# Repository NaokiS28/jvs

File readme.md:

# JVS ArduinIO
This is a WIP library for communicating over the JVS protocol in Arduino compatible boards. This library supports both host mode and device mode. It requires one hardware UART to work connected to an RS485 transceiver such as the MAX RS485 TTL converter module.

A host can only have 1 input port per instance, a device must have 1 ouput port but may optionally have an input port for daisy chaning IO devices. The data lines are connected between ports, the sense line must connect to an output for the output port and an input for the input port. You will also need to connect the sense pin to pin 1 of USB-A connector.

# Hardware
## Device mode
This library requires a MAX485 transceiver or equivalent connected to the serial port RX and TX pins. You also need to specify an RTS (Request to Send) pin which is connected to both DE and ~RE.

Finally, you will either need a transistor (BC547 or 2n2222 or eqv.) for pulling the sense line low; whilst you can use the IO pin directly, it is better practice to do it this way to protect your MCU and the library would need to be changed to uninvert the pin. The sense line needs to be at 2.5v with the ID unset, and it's recomended to use 4x 1n4007 diodes from the sense line to ground to acheive this but users have reported a 1K resistor will also work - This will depend entirely on the host you are using.

Optionally you can specify a sense input line but this isn't unless you are supporting daisy chaining. If you are, you need a way to automatically terminate or remove the termination resistors from the bus. The bus must be terminated if there is no secondary IO board attached. It must *not* be terminated if there is a secondary IO board attached to your device.

Here is an example with downstream IO sensing which is needed for daisychaining.

## Host mode
In host mode, it is advised to use an LM393 opamp to handle 5V, 2.5v and 0v sensing. This allows one to use either two pin or one pin to sense IO status (present with/out ID, not present). Otherwise, you can connect this to a GPIO pin, perhaps use a 220Ω resistor in line for over current protection.

### Sensing
Depending on how you want to sense IO boards, you will need to consider different methods of sensing the IO board attached.

The SEGA/Nintendo/Namco Triforce does single pin sensing which is good enough for most use cases:

Another option is to remove the buffer gate and use two pins for better sensing. This allows one to know exactly the state of the sense in pin, be it IO board not connected, IO is present with no ID or present and ID'd. The SEGA Chihiro uses a verison of this sensing:

# Usage
To use the library, include it before setup and then declare an instance by passing a UART port and the sense pin input/output. On Arduino UNO this will be Serial, but on board with multiple serial ports, you can use Serial2, Serial 3 etc. You cannot use SerialUSB. **Note you can only have one instance at one time**.
```
#include "jvs.h"
JVS jvs(Serial, 2, 3);     // HardwareSerial port, Sense pin, RTS pin
```
Once delcared, you will then need to run the initialization routines at startup either as a host node or a device node.
```
// Init as Device
void setup(){
    jvs.begin(DEVICE_NODE);    // Begin as device node
    jvs.initDevice();
}
```
```
// Init as Host
void setup(){
    jvs.begin(HOST_NODE);    // Begin as host node
    int found = jvs.initHost();       // Will hang here until devices are assigned or there is no JVS nodes. Returns number of JVS nodes
    //Serial1.print("Found: ");
    //Serial1.print(found);
    //Serial1.println(" nodes");
}
```
Then you will need to put update() in your loop. This is so you can receive packets from the IO board. You can have the JVS library run command codes, so long as it's in device mode and have set the iput/output data arrays:
```
void loop(){
    if(jvs.update()){
        jvs.runCommand();
    }
}
```
Or you can read the data in manually:
```
void loop(){
    if(jvs.update()){
        JVS_Frame inFrame;      // Frame in
        inFrame = jvs.read();   // Read frame into buffer
    }
}
```

## Data Storage/JVS Frame layout
The data for commands and arguments is stored in JVS_Frame.data:
```
struct JVS_Frame {
    uint8_t sync = 0xE0;            // Sync is always E0
    uint8_t nodeID = 0;             // Node that frame is intended for, 0xFF is a boradcast frame
    uint8_t numBytes = 0;           // Includes all subsequent bytes (Status, data and sum) in frame after this byte
    uint8_t statusCode = 1;
    union{
        uint8_t data [254] = {0};   // Is command and parameters from host, report and results from device
        uint16_t data16 [127];      // Some parameters are 16-bit ints
        char dataString [102];      // When reading node IDs, they are stored as ASCII
    } ;
    uint8_t sum = 0;                // Checksum of ID, numbytes, data bytes
    uint8_t cmdCount = 1;           // Number of commands counted. Only counts standard commands (not manufacturer specific)
};
```

## JVS Info
Both host and device nodes will need some data to report back when requested. The host needs the game name filled in where as devices need to report their name and what features it supports. If no data is supplied, it is prefilled with generic data. **Note: When set as device, _ident is used where as _mainID is used when set to host**. It's worth noting that only Namco games/devices seem to care about the main board ID, you can choose to support it or not, but Namco games might not be happy if you don't support it.

The library supports storing JVS IO board data in the following struct. This can be used for multiple IO boards by delcaring an array.
```
struct JVS_Info {
    char ident[100] = {"JVS ArduinIO;github.com/NaokiS28/jvs;VER:0.1 Beta"};
    char mainID[100] = {"ArduinoIO Host;github.com/NaokiS28/jvs;VER:0.1 Beta"};
    uint8_t cmdRev = 11;            // Stored as BCD, some JVS hosts (Triforce) will report ver 0.0 if it's higher than 1.1
    uint8_t jvsRev = 30;            // Stored as BCD, JVS rev. 20 and 30 are valid
    uint8_t comRev = 10;            // Stored as BCD, use 10 unless you need to otherwise
    uint8_t totalFeatures = 4;      // How many features supported, this isnt sent to the host but for the library
    featureTypes featureSupport[16] = {
        switchInput, coinInput, analogInput, gpOutput       // Supported features. These are listed in jvs_message.h
    };
    uint8_t featureParameters[16][3] = {                    // Parameters for the list of supported features.
        {2, 12, 0},     // Is switchInput in generic construction
        {2, 0, 0},      // 2 Coin slots
        {6, 10, 0},     // 6 ADCs, 10-Bit resolution
        {8, 0, 0}       // 8 GPOs (general purpose output)
    };
};
```

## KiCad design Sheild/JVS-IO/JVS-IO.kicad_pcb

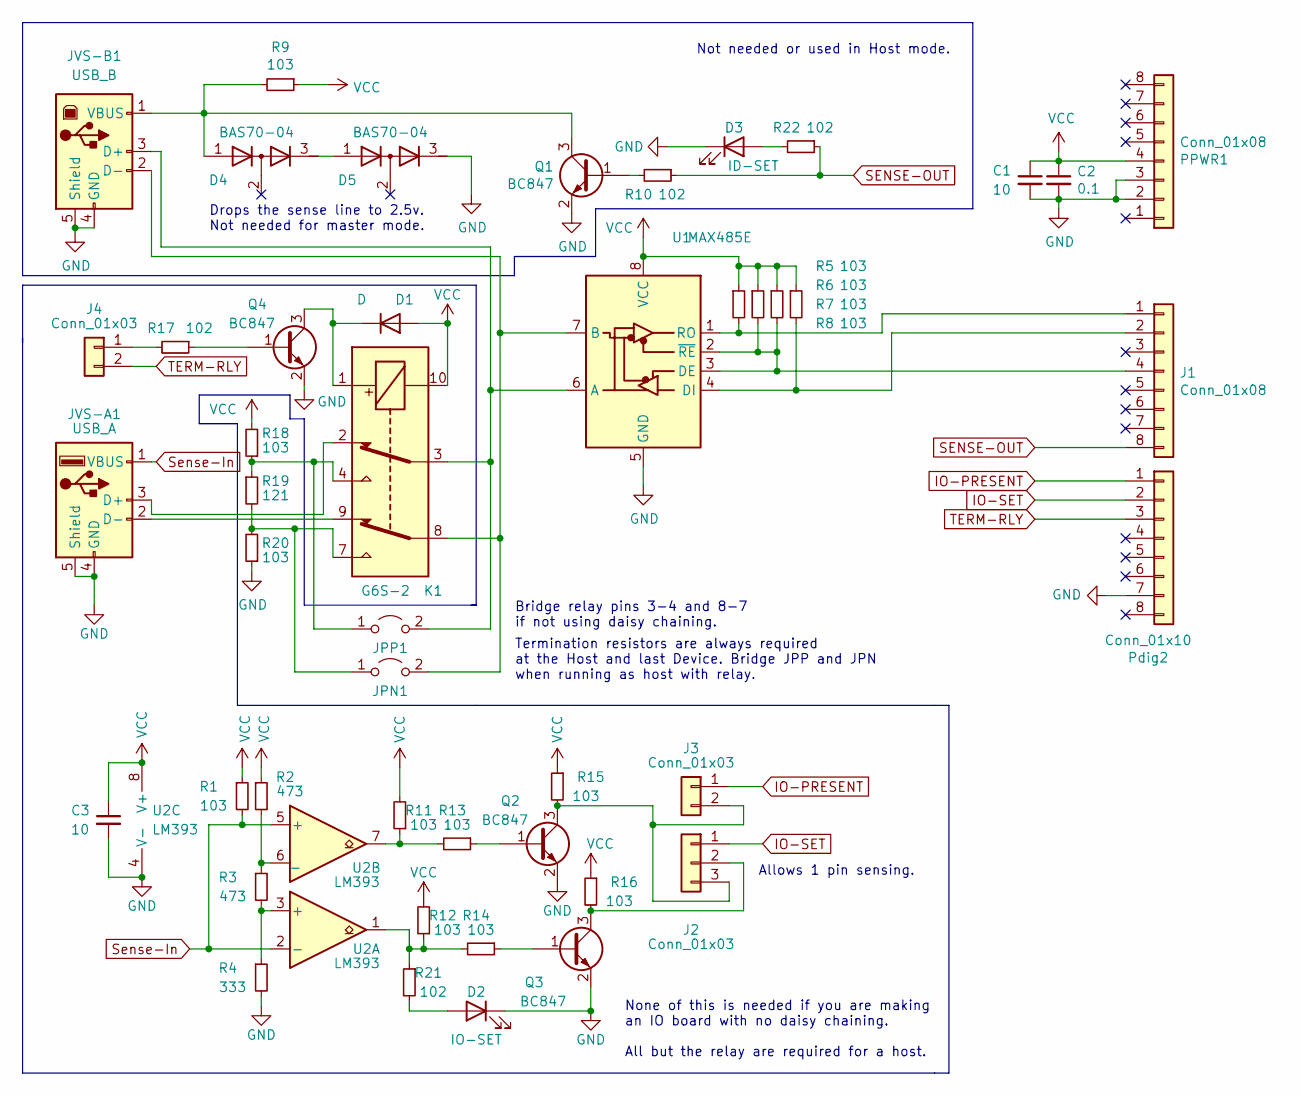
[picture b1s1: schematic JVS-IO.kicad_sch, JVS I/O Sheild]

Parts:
C1, C3: 10; C_1206_3216Metric
C2: 0.1; C_1206_3216Metric
D1: D; D_1206_3216Metric
D2: IO-SET; LED_1206_3216Metric
D3: ID-SET; LED_1206_3216Metric
D4, D5: BAS70-04; SOT-23
J1: Conn_01x08; PinHeader_1x08_P2.54mm_Vertical
J2: Conn_01x03; PinHeader_1x03_P2.54mm_Vertical
J3, J4: Conn_01x03; PinHeader_1x02_P2.54mm_Vertical
JPN1: Jumper_2_Open; SolderJumper-2_P1.3mm_Open_Pad1.0x1.5mm
JPP1: Jumper_2_Open; SolderJumper-2_P1.3mm_Open_Pad1.0x1.5mm
JVS-A1: USB_A; USB_A_CONNFLY_DS1095-WNR0
JVS-B1: USB_B; USB_B_Lumberg_2411_02_Horizontal
K1: G6S-2; Relay_DPDT_Omron_G6S-2
PPWR1: Conn_01x08; PinHeader_1x08_P2.54mm_Vertical
Pdig2: Conn_01x10; PinHeader_1x10_P2.54mm_Vertical
Q1, Q2, Q3, Q4: BC847; SOT-23
R1, R5, R6, R7, R8, R9, R11, R12, R13, R14, R15, R16, R18, R20: 103; R_1206_3216Metric
R2, R3: 473; R_1206_3216Metric
R4: 333; R_1206_3216Metric
R10, R17, R21, R22: 102; R_1206_3216Metric
R19: 121; R_1206_3216Metric
U1: MAX485E; SOIC-8_3.9x4.9mm_P1.27mm
U2: LM393; SOIC-8_3.9x4.9mm_P1.27mm

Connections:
GND: C1.2, C2.2, C3.2, D2.1 (K), D3.1 (K), D5.3 (K), JVS-A1.4 (GND), JVS-A1.5 (Shield), JVS-B1.4 (GND), JVS-B1.5 (Shield), PPWR1.2, PPWR1.3, Pdig2.7, Q1.2 (E), Q2.2 (E), Q3.2 (E), Q4.2 (E), R4.2, R20.1, U1.5 (GND), U2.4 (V-)
IO-PRESENT: J3.1, Pdig2.1
IO-SET: J2.1, Pdig2.2
unnamed: D1.1 (K), K1.1, Q4.3 (C)
unnamed: D2.2 (A), R21.2
unnamed: D3.2 (A), R22.2
unnamed: D4.3 (K), D5.1 (A)
unnamed: J1.1, R5.2, U1.1 (RO)
unnamed: J1.2, R8.2, U1.4 (DI)
unnamed: J1.4, R6.2, R7.2, U1.2 (~RE), U1.3 (DE)
unnamed: J2.2, Q3.3 (C), R16.2
unnamed: J2.3, J3.2, Q2.3 (C), R15.2
unnamed: J4.1, R17.2
unnamed: JVS-A1.2 (D-), K1.9
unnamed: JVS-A1.3 (D+), K1.2
unnamed: D4.1 (A), JVS-B1.1 (VBUS), Q1.3 (C), R9.2
unnamed: JPN1.2 (B), JVS-B1.2 (D-), K1.8, U1.7 (B)
unnamed: JPP1.2 (B), JVS-B1.3 (D+), K1.3, U1.6 (A)
unnamed: JPP1.1 (A), K1.4, R18.1, R19.1
unnamed: JPN1.1 (A), K1.7, R19.2, R20.2
unnamed: Q1.1 (B), R10.2
unnamed: Q2.1 (B), R13.1
unnamed: Q3.1 (B), R14.1
unnamed: Q4.1 (B), R17.1
unnamed: R2.2, R3.1, U2.6 (_)
unnamed: R3.2, R4.1, U2.3 (+)
unnamed: R11.1, R13.2, U2.7
unnamed: R12.1, R14.2, R21.1, U2.1
SENSE-OUT: J1.8, R10.1, R22.1
Sense-In: JVS-A1.1 (VBUS), R1.2, U2.2 (-), U2.5 (+)
TERM-RLY: J4.2, Pdig2.3
VCC: C1.1, C2.1, C3.1, D1.2 (A), K1.10, PPWR1.4, R1.1, R2.1, R5.1, R6.1, R7.1, R8.1, R9.1, R11.2, R12.2, R15.1, R16.1, R18.2, U1.8 (VCC), U2.8 (V+)

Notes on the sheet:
Not needed or used in Host mode.
None of this is needed if you are making an IO board with no daisy chaining. All but the relay are required for a host.
Bridge relay pins 3-4 and 8-7 if not using daisy chaining.
Allows 1 pin sensing.
Drops the sense line to 2.5v. Not needed for master mode.
Termination resistors are always required at the Host and last Device. Bridge JPP and JPN when running as host with relay.

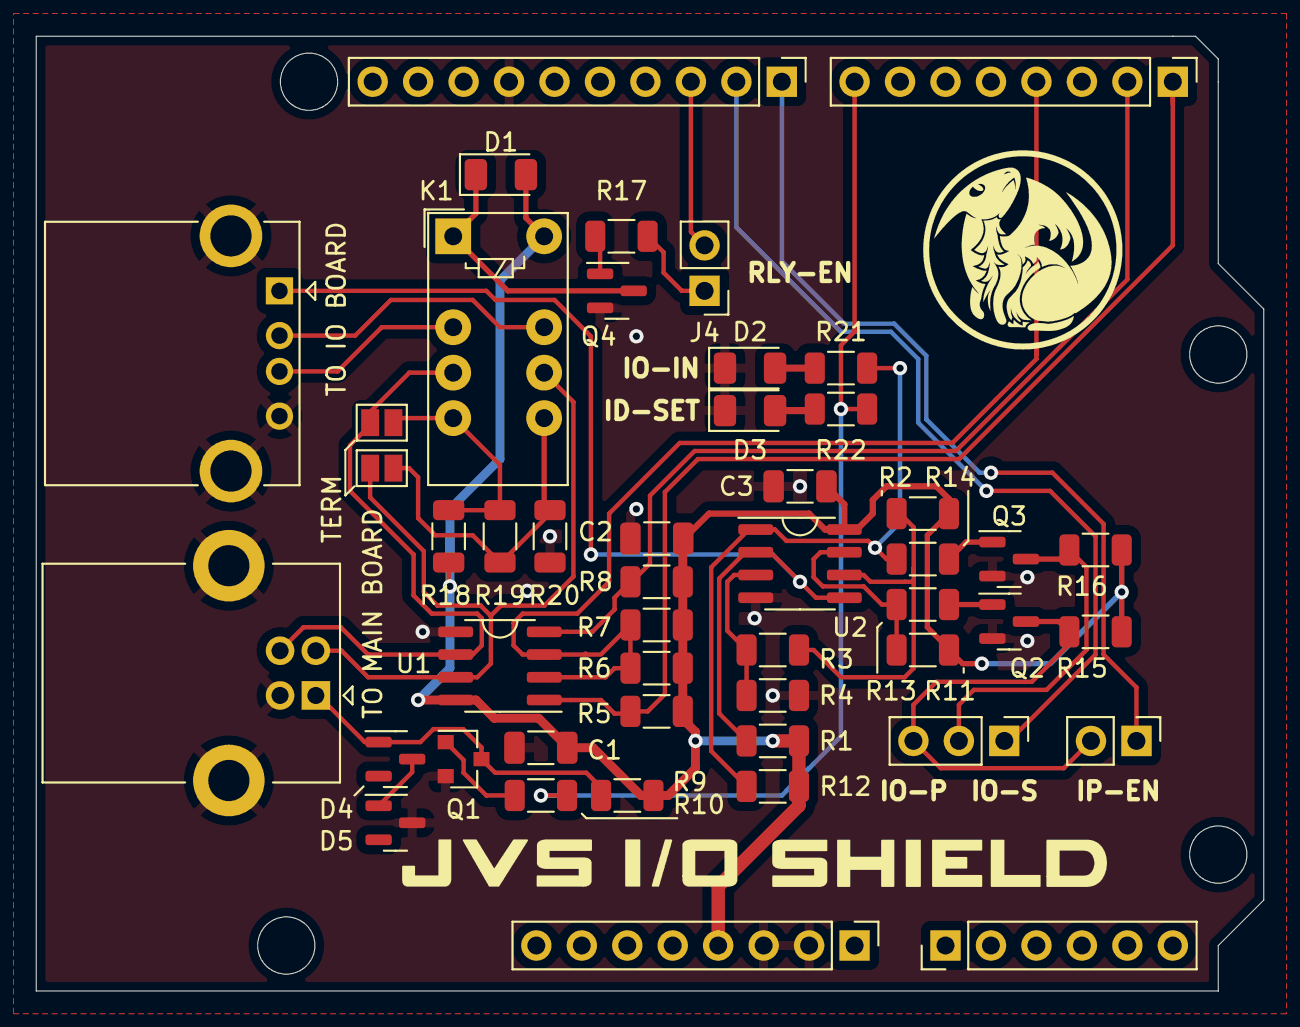
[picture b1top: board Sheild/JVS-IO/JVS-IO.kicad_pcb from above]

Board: 2 copper layers, 68.6 x 53.3 mm, 47 parts (0 on the bottom side), 32 nets.

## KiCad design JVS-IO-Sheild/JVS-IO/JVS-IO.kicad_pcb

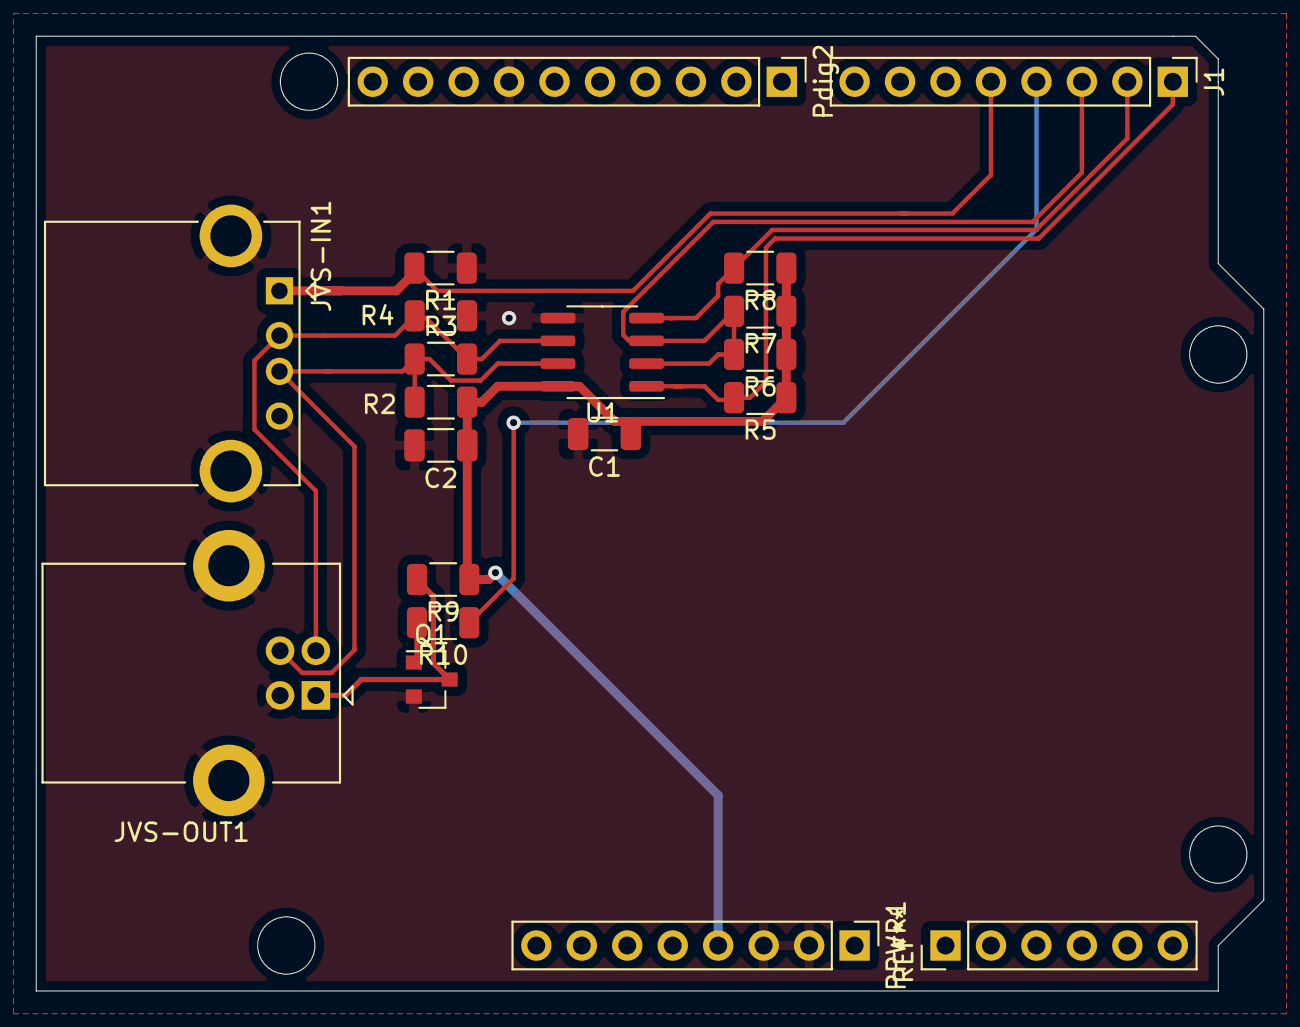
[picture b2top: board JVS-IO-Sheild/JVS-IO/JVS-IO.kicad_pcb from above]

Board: 2 copper layers, 68.6 x 53.3 mm, 19 parts (0 on the bottom side), 11 nets.

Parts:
C1: 10; C_1206_3216Metric
C2: 0.1; C_1206_3216Metric
J1: Conn_01x08; PinHeader_1x08_P2.54mm_Vertical
JVS-IN1: USB_A; USB_A_CONNFLY_DS1095-WNR0
JVS-OUT1: USB_B; USB_B_Lumberg_2411_02_Horizontal
PPWR1: Conn_01x08; PinHeader_1x08_P2.54mm_Vertical
Pdig2: Conn_01x10; PinHeader_1x10_P2.54mm_Vertical
Q1: BC847; SOT-23
R1: R_Small; R_1206_3216Metric
R2, R4: 203; R_1206_3216Metric
R3: 121; R_1206_3216Metric
R5, R6, R7, R8, R9: 103; R_1206_3216Metric
R10: 102; R_1206_3216Metric
U1: MAX485E; SOIC-8_3.9x4.9mm_P1.27mm

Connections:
GND: C1.2, C2.2, JVS-IN1.4, JVS-IN1.5, JVS-OUT1.4, JVS-OUT1.5, PPWR1.2, PPWR1.3, Pdig2.7, Q1.2, R1.1, R4.1, U1.5
unnamed: J1.1, R5.2, U1.1
unnamed: J1.2, R8.2, U1.4
unnamed: J1.3, R6.2, R7.2, U1.2, U1.3
unnamed: J1.4, R10.1
unnamed: JVS-IN1.2, JVS-OUT1.2, R3.2, R4.2, U1.6
unnamed: JVS-IN1.3, JVS-OUT1.3, R2.2, R3.1, U1.7
unnamed: JVS-OUT1.1, Q1.3, R9.2
unnamed: Q1.1, R10.2
VCC: C1.1, C2.1, PPWR1.4, R2.1, R5.1, R6.1, R7.1, R8.1, R9.1, U1.8
~SENSE-OUT: J1.5, JVS-IN1.1, R1.2

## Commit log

2021-08-22 Updated readme and some documentation
2021-08-22 Added PCB
2021-09-12 Functioning but mostly incomplete code
    Library can now talk as a device to a host, tested with SEGA Triforce Type 1. Much work and testing to be done with command support, examples and host mode.
2021-09-12 Fixed bugs with pointers in sendSwitches
2021-09-12 Minor: Ignore VS Code workspace
2021-09-12 Updated docs with more infomation
2021-09-12 Fix image bug
2021-09-12 Bug in imahes
2021-09-17 Working prototype for Switches and Coins
    runCommand now correctly parses switch inputs from given array, including cabinet controls and coin slots.
    Coin counters *should* work but need to be tested further.
2021-09-29 Master mode improvements
    Master Mode is working and is relatively easy to use now
2021-09-29 Added Master info reader and packet sniffer
    JVS_dump does not use the JVS library, it is merely designed to write byte values from the bus to monitor
2021-10-31 Blank out JVS_Message struct
    Having prefilled data was causing issues so until I can figure out how to do it better, it's blanked out
2021-11-29 Minor changes, no longer using circular buffer
2021-12-05 Fixed library so mark bytes are properly decoded.
2022-10-13 Major update. Sheild made.
2022-10-16 Fixed errant bugs
2022-12-07 Updated library to use newer init procedure
2023-12-29 Inputs working over JVS
2023-12-30 Input and Output working on JVS
2024-04-29 Functionally complete
